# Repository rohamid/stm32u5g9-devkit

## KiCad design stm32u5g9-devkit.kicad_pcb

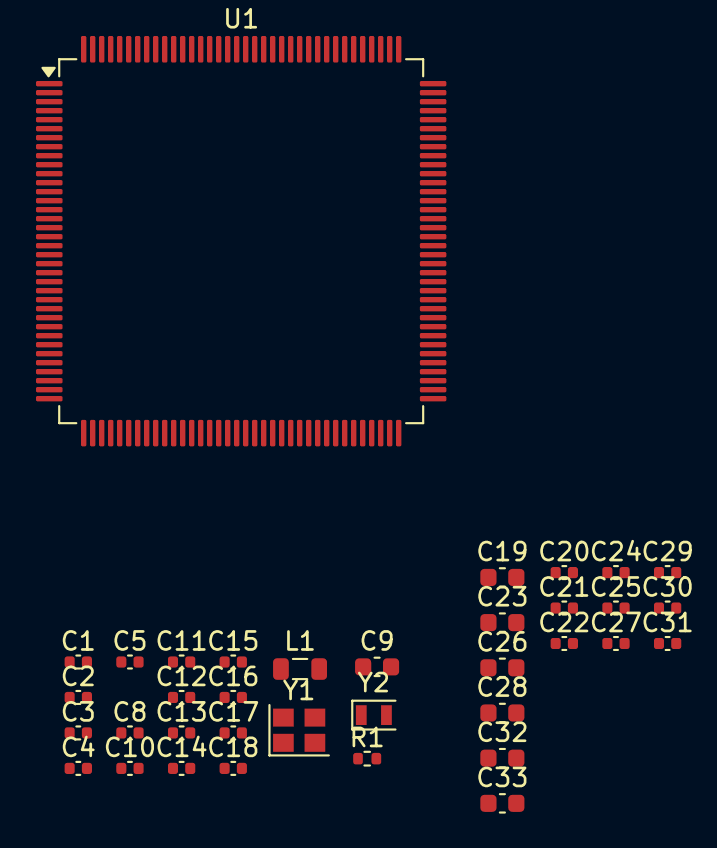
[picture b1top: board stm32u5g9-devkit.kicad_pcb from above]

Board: 2 copper layers, 36 parts (0 on the bottom side), 9 nets, no tracks yet.

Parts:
C1, C2, C3, C4: 22p; C_0402_1005Metric
C5, C8, C10, C11, C12, C13, C14, C15, C16, C17, C18, C20, C21, C22, C24, C25, C27, C29, C30, C31: 100n; C_0402_1005Metric
C9, C23: 10u; C_0603_1608Metric
C19: 4u7; C_0603_1608Metric
C26, C28: 1u; C_0603_1608Metric
C32, C33: 2u2; C_0603_1608Metric
L1: 2u2; L_0805_2012Metric
R1: 10K; R_0402_1005Metric
U1: STM32U5G9ZJTxQ; LQFP-144_20x20mm_P0.5mm
Y1: 16MHz; Crystal_SMD_2520-4Pin_2.5x2.0mm
Y2: 32.768KHz; Crystal_SMD_2012-2Pin_2.0x1.2mm

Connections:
+3V3: C8.1, C9.1, C10.1, C11.1, C12.1, C13.1, C14.1, C15.1, C16.1, C17.1, C18.1, C19.1, C20.1, C21.1, C22.1, C23.1, C24.1, C25.1, C26.1, C27.1, C28.1, C29.1, R1.1, U1.13 (VDDDSI), U1.25 (VDD), U1.34 (VREF+), U1.35 (VDDA), U1.41 (VDD), U1.55 (VDD), U1.65 (VDDSMPS), U1.69 (VDD), U1.83 (VDD), U1.89 (VDD), U1.95 (VDD), U1.108 (VDDUSB), U1.109 (VDD), U1.122 (VDD), U1.131 (VDDIO2), U1.144 (VDD)
/MCU/RCC_OSC32_IN: C3.2, U1.8 (RCC_OSC32_IN), Y2.2
/MCU/RCC_OSC32_OUT: C4.2, U1.9 (RCC_OSC32_OUT), Y2.1
/MCU/RCC_OSC_IN: C1.2, Y1.3
/MCU/RCC_OSC_OUT: C2.2, Y1.1
/MCU/RESET: C5.2, R1.2, U1.28 (NRST)
GND: C1.1, C2.1, C3.1, C4.1, C5.1, C8.2, C9.2, C10.2, C11.2, C12.2, C13.2, C14.2, C15.2, C16.2, C17.2, C18.2, C19.2, C20.2, C21.2, C22.2, C23.2, C24.2, C25.2, C26.2, C27.2, C28.2, C29.2, C30.2, C31.2, C32.2, C33.2, U1.17 (VSSDSI), U1.23 (VSSDSI), U1.24 (VSS), U1.33 (VSSA), U1.40 (VSS), U1.54 (VSS), U1.66 (VSSSMPS), U1.68 (VSS), U1.82 (VSS), U1.88 (VSS), U1.94 (VSS), U1.110 (VSS), U1.130 (VSS), U1.143 (VSS), Y1.2, Y1.4
unnamed: L1.2, U1.64 (VLXSMPS)
VDD11: C30.1, C31.1, C32.1, C33.1, L1.1, U1.14 (VDD11DSI), U1.20 (VDD11DSI), U1.67 (VDD11), U1.142 (VDD11)

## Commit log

2024-09-22 Add Octospi Flash, LCD 40P, 50P, MIPI
